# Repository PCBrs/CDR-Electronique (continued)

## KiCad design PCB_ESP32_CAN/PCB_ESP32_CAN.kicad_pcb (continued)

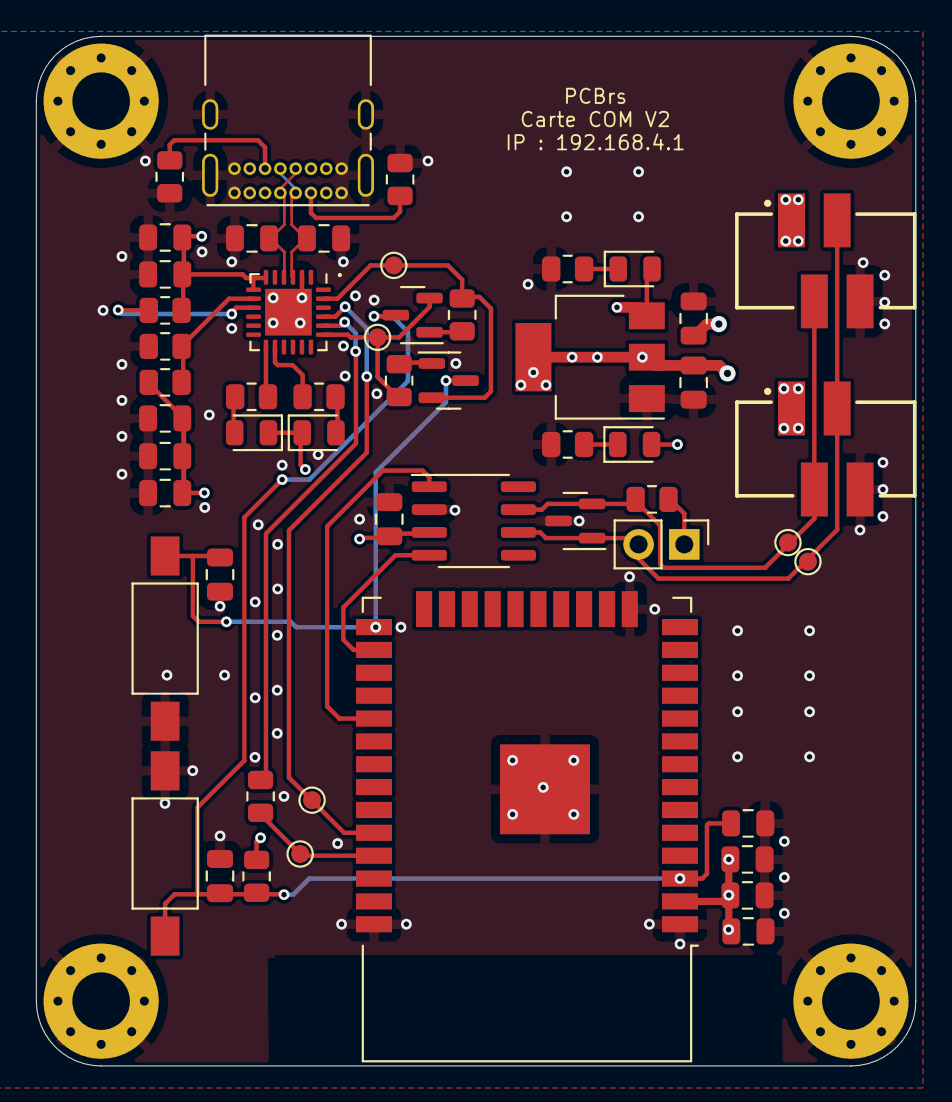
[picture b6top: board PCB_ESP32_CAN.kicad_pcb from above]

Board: 4 copper layers, 48.9 x 57.2 mm, 57 parts (0 on the bottom side), 29 nets.

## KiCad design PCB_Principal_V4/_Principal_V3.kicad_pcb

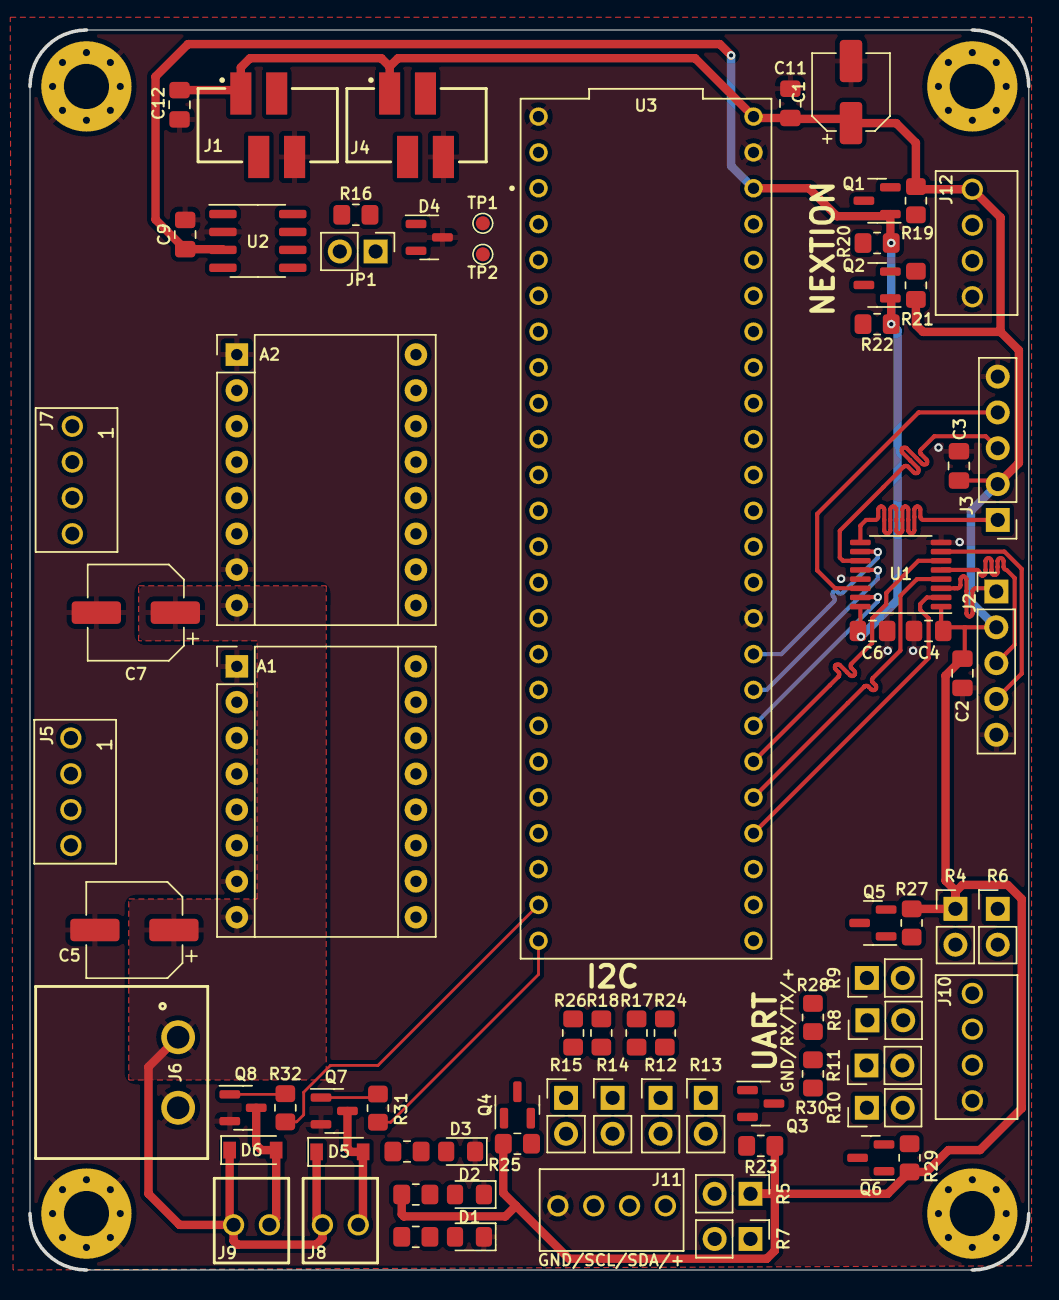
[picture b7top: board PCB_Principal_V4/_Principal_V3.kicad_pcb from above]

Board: 2 copper layers, 70.8 x 87.9 mm, 80 parts (0 on the bottom side), 67 nets.

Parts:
A1, A2: Pololu_Breakout_DRV8825; Pololu_Breakout-16_15.2x20.3mm
C1: 10u; CP_Elec_5x5.4
C2, C3, C4, C6, C9, C11: 100n; C_0805_2012Metric_Pad1.18x1.45mm_HandSolder
C5, C7: 47u; CP_Elec_6.3x5.4
C12: 10u; C_0805_2012Metric_Pad1.18x1.45mm_HandSolder
D1, D2, D3: LED; LED_0805_2012Metric_Pad1.15x1.40mm_HandSolder
D4: TVS; SOT-23
D5, D6: 1N4148W; D_SOD-123
H1, H2, H3, H4: MountingHole_Pad; MountingHole_3.2mm_M3_Pad_Via
J1, J4: CAN; 690367290476
J2: ENCODEUR_G; PinHeader_1x05_P2.54mm_Vertical
J3: ENCODEUR_D; PinHeader_1x05_P2.54mm_Vertical
J5: MOTOR_D; Wuerth_2.54mm_4pins_61900411121
J6: BATT; Wuerth_batcon_691313710002
J7: MOTOR_G; Wuerth_2.54mm_4pins_61900411121
J8, J9: FAN; Wuerth_2.54mm_2pins_61900211121
J10: UART; Wuerth_2.54mm_4pins_61900411121
J11: I2C; Wuerth_2.54mm_4pins_61900411121
J12: NEXTION; Wuerth_2.54mm_4pins_61900411121
JP1: 120; PinHeader_1x02_P2.54mm_Vertical
Q1, Q2, Q3, Q4, Q5, Q6: SI2302S; SOT-23
Q7, Q8: Q_NPN_BEC; SOT-23
R1, R17, R18: 4.7k; R_0805_2012Metric_Pad1.20x1.40mm_HandSolder
R2: 560; R_0805_2012Metric_Pad1.20x1.40mm_HandSolder
R3: 220; R_0805_2012Metric_Pad1.20x1.40mm_HandSolder
R4, R5, R6, R7, R8, R9, R10, R11, R12, R13, R14, R15: 0; PinHeader_1x02_P2.54mm_Vertical
R16: 120; R_0805_2012Metric_Pad1.20x1.40mm_HandSolder
R19, R20, R21, R22, R23, R24, R25, R26, R27, R28, R29, R30, R31, R32: 10k; R_0805_2012Metric_Pad1.20x1.40mm_HandSolder
TP1: CANH; TestPoint_Pad_D1.0mm
TP2: CANL; TestPoint_Pad_D1.0mm
U1: 4504; TSSOP-16_4.4x5mm_P0.65mm
U2: SN65HVD232; SOIC-8_3.9x4.9mm_P1.27mm
U3: TEENSY 4.1; Teensy_4-1

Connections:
+3V3: C6.2, C9.2, Q1.1 (G), Q2.1 (G), Q3.1 (G), Q4.1 (G), Q5.1 (G), Q6.1 (G), R3.1, R6.1, R7.1, R17.1, R18.1, R20.2, R22.2, R24.2, R26.2, R28.2, R30.2, U1.16 (VDD), U2.3 (VCC), U3.3.3V_1 (3.3V), U3.3.3V_2 (3.3V)
+5V: C1.1, C2.1, C3.1, C4.2, C11.1, C12.1, J1.1, J2.2, J3.2, J4.1, J12.1, R2.1, R4.1, R5.1, R19.2, R21.2, R23.2, R25.2, R27.2, R29.2, U1.1 (VCC), U3.VIN
+24V: A1.8 (VMOT), A2.8 (VMOT), C5.1, C7.1, D5.1 (K), D6.1 (K), J6.1, J8.1, J9.1, R1.1
/CANH: D4.1 (A1), J1.2, J4.2, R16.1, TP1.1, U2.7 (CANH)
/CANL: D4.2 (A2), J1.3, J4.3, JP1.2, TP2.1, U2.6 (CANL)
/CHANNEL_A_D: U1.12 (Eout), U3.40 (A16)
/CHANNEL_A_G: U1.4 (Bout), U3.37 (CS3)
/CHANNEL_B_D: U1.10 (Dout), U3.41 (A17)
/CHANNEL_B_G: U1.2 (Aout), U3.36 (CS2)
/CHANNEL_IDX_D: U1.15 (Fout), U3.39 (A15)
/CHANNEL_IDX_G: U1.6 (Cout), U3.38 (A14)
/DIR_D: A1.16 (DIR), U3.10 (CS1)
/DIR_G: A2.16 (DIR), U3.2 (OUT2)
/EN_D: A1.9 (~EN), U3.12 (MISO)
/EN_G: A2.9 (~EN), U3.4 (BCLK2)
/Level_shifter/IN: J12.2, J12.3, Q1.2 (D), Q2.2 (D), Q3.2 (D), Q4.2 (D), Q5.2 (D), Q6.2 (D), R9.1, R11.1, R13.1, R15.1, R19.1, R21.1, R23.1, R25.1, R27.1, R29.1
/M0_D: A1.10 (M0), U3.28 (RX7)
/M0_G: A2.10 (M0), U3.9 (OUT1C)
/M1_D: A1.11 (M1), U3.27 (A13)
/M1_G: A2.11 (M1), U3.8 (TX2)
/M2_D: A1.12 (M2), U3.26 (A12)
/M2_G: A2.12 (M2), U3.7 (RX2)
/NEXTION_RX: Q1.3 (S), R20.1, U3.0 (RX1)
/NEXTION_TX: Q2.3 (S), R22.1, U3.1 (TX1)
/PWM_FAN1: R31.1, U3.32 (OUT1B)
/PWM_FAN2: R32.1, U3.31 (CTX3)
/RST_D: A1.13 (~RST), U3.25 (A11)
/RST_G: A2.13 (~RST), U3.6 (OUT1D)
/RX: Q6.3 (S), R10.1, R30.1, U3.14 (A0)
/RX_CAN: U2.4 (R), U3.23 (A9)
/S1_D: J3.1, U1.9 (Din)
/S1_G: J2.1, U1.3 (Ain)
/S2_D: J3.3, U1.11 (Ein)
/S2_G: J2.3, U1.5 (Bin)
/S3_D: J3.4, U1.14 (Fin)
/S3_G: J2.4, U1.7 (Cin)
/SCL: Q4.3 (S), R14.1, R18.2, R26.1, U3.19 (A5)
/SDA: Q3.3 (S), R12.1, R17.2, R24.1, U3.18 (A4)
/SLP_D: A1.14 (~SLP), U3.24 (A10)
/SLP_G: A2.14 (~SLP), U3.5 (IN2)
/STP_D: A1.15 (STEP), U3.11 (MOSI)
/STP_G: A2.15 (STEP), U3.3 (LRCLK2)
/TX: Q5.3 (S), R8.1, R28.1, U3.15 (A1)
/TX_CAN: U2.1 (D), U3.22 (A8)
GND: A1.1 (GND), A1.7 (GND), A2.1 (GND), A2.7 (GND), C1.2, C2.2, C3.2, C4.1, C5.2, C6.1, C7.2, C9.1, C11.2, C12.2, D1.1 (K), D2.1 (K), D3.1 (K), D4.3 (common), H1.1, H2.1, H3.1, H4.1, J1.4, J2.5, J3.5, J4.4, J6.2, J10.4, J11.4, J12.4, Q7.2 (E), Q8.2 (E), U1.8 (VSS), U1.13 (Select), U2.2 (GND), U3.GND1 (GND), U3.GND2 (GND), U3.GND3 (GND)
unnamed: A1.3 (A2), J5.1
unnamed: A1.4 (A1), J5.2
unnamed: A1.5 (B1), J5.3
unnamed: A1.6 (B2), J5.4
unnamed: A2.3 (A2), J7.1
unnamed: A2.4 (A1), J7.2
unnamed: A2.5 (B1), J7.3
unnamed: A2.6 (B2), J7.4
unnamed: D1.2 (A), R1.2
unnamed: D2.2 (A), R2.2
unnamed: D3.2 (A), R3.2
unnamed: D5.2 (A), J8.2, Q7.3 (C)
unnamed: D6.2 (A), J9.2, Q8.3 (C)
unnamed: J10.1, R4.2, R6.2
unnamed: J10.2, R8.2, R9.2
unnamed: J10.3, R10.2, R11.2
unnamed: J11.1, R5.2, R7.2
unnamed: J11.2, R12.2, R13.2
unnamed: J11.3, R14.2, R15.2
unnamed: JP1.1, R16.2
unnamed: Q7.1 (B), R31.2
unnamed: Q8.1 (B), R32.2

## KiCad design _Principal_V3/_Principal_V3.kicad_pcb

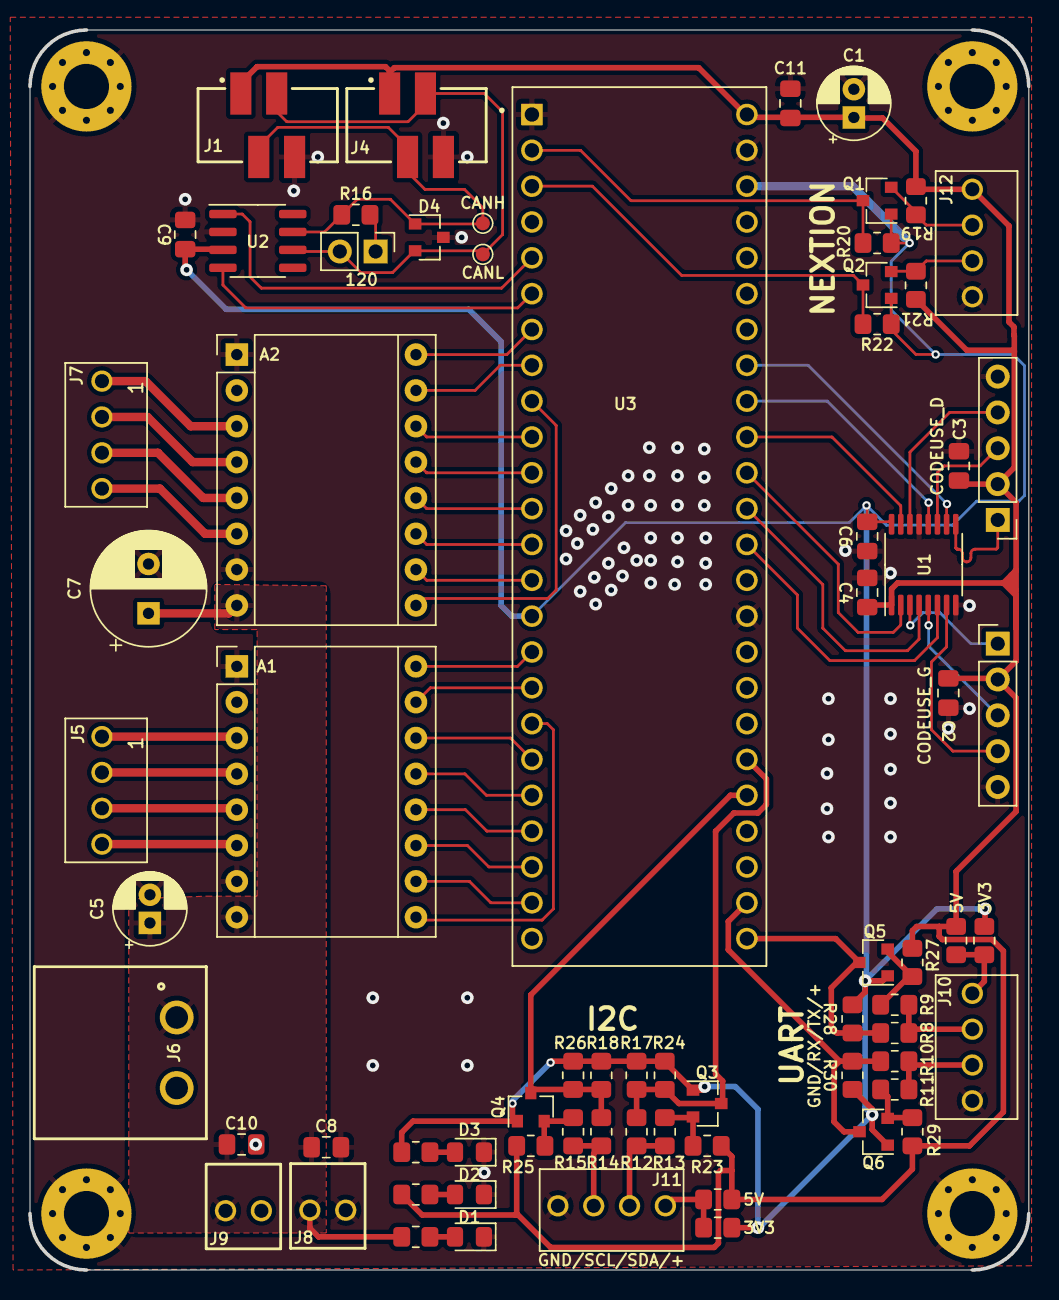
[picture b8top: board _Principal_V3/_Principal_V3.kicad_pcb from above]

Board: 2 copper layers, 70.8 x 87.9 mm, 75 parts (0 on the bottom side), 66 nets.

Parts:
3V3, 3V3#2, 5V, 5V#2: 0; R_0805_2012Metric_Pad1.20x1.40mm_HandSolder
120: 120; PinHeader_1x02_P2.54mm_Vertical
A1, A2: Pololu_Breakout_DRV8825; Pololu_Breakout-16_15.2x20.3mm
C1, C5: 10u; CP_Radial_D5.0mm_P2.00mm
C2, C3, C4, C6, C9, C11: 100n; C_0805_2012Metric_Pad1.18x1.45mm_HandSolder
C7: 10u; CP_Radial_D8.0mm_P3.50mm
C8, C10: 10u; C_0805_2012Metric_Pad1.18x1.45mm_HandSolder
CANH: CANH; TestPoint_Pad_D1.0mm
CANL: CANL; TestPoint_Pad_D1.0mm
CODEUSE_D: ENCODEUR_D; PinHeader_1x05_P2.54mm_Vertical
CODEUSE_G: ENCODEUR_G; PinHeader_1x05_P2.54mm_Vertical
D1, D2, D3: LED; LED_0805_2012Metric_Pad1.15x1.40mm_HandSolder
D4: TVS; SOT-23
H1, H2, H3, H4: MountingHole_Pad; MountingHole_3.2mm_M3_Pad_Via
J1, J4: CAN; 690367290476
J5: MOTOR_D; Wuerth_2.54mm_4pins_61900411121
J6: BATT; Wuerth_batcon_691313710002
J7: MOTOR_G; Wuerth_2.54mm_4pins_61900411121
J8, J9: FAN; Wuerth_2.54mm_2pins_61900211121
J10: UART; Wuerth_2.54mm_4pins_61900411121
J11: I2C; Wuerth_2.54mm_4pins_61900411121
J12: NEXTION; Wuerth_2.54mm_4pins_61900411121
Q1, Q2, Q3, Q4, Q5, Q6: SI2302S; SOT-23
R1, R17, R18: 4.7k; R_0805_2012Metric_Pad1.20x1.40mm_HandSolder
R2: 560; R_0805_2012Metric_Pad1.20x1.40mm_HandSolder
R3: 220; R_0805_2012Metric_Pad1.20x1.40mm_HandSolder
R8, R9, R10, R11, R12, R13, R14, R15: 0; R_0805_2012Metric_Pad1.20x1.40mm_HandSolder
R16: 120; R_0805_2012Metric_Pad1.20x1.40mm_HandSolder
R19, R20, R21, R22, R23, R24, R25, R26, R27, R28, R29, R30: 10k; R_0805_2012Metric_Pad1.20x1.40mm_HandSolder
U1: 4504; TSSOP-16_4.4x5mm_P0.65mm
U2: SN65HVD232; SOIC-8_3.9x4.9mm_P1.27mm
U3: DEV-14058; MODULE_DEV-14058

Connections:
+3V3: 3V3.1, 3V3#2.1, C6.2, C9.2, Q1.1 (G), Q2.1 (G), Q3.1 (G), Q4.1 (G), Q5.1 (G), Q6.1 (G), R3.1, R17.1, R18.1, R20.2, R22.2, R24.2, R26.2, R28.2, R30.2, U1.16 (VDD), U2.3 (VCC), U3.15 (3V3), U3.46 (3V3_250MA_MAX)
+5V: 5V.1, 5V#2.1, C1.1, C2.1, C3.1, C4.2, C11.1, CODEUSE_D.2, CODEUSE_G.2, J1.1, J4.1, J12.1, R2.1, R19.2, R21.2, R23.2, R25.2, R27.2, R29.2, U1.1 (VCC), U3.48 (VIN)
+24V: A1.8 (VMOT), A2.8 (VMOT), C5.1, C7.1, C8.1, C10.1, J6.1, J8.1, J9.1, R1.1
/CANH: CANH.1, D4.1 (A1), J1.2, J4.2, R16.1, U2.7 (CANH)
/CANL: 120.2, CANL.1, D4.2 (A2), J1.3, J4.3, U2.6 (CANL)
/CHANNEL_A_D: U1.12 (Eout), U3.40 (18/A4/SDA0/TOUCH)
/CHANNEL_A_G: U1.4 (Bout), U3.37 (15/A1/CS0/TOUCH)
/CHANNEL_B_D: U1.10 (Dout), U3.41 (19/A5/SCL0/TOUCH)
/CHANNEL_B_G: U1.2 (Aout), U3.38 (16/A2/PWM/SCL0/TOUCH)
/CHANNEL_IDX_D: U1.15 (Fout), U3.39 (17/A3/PWM/SDA0/TOUCH)
/CHANNEL_IDX_G: U1.6 (Cout), U3.36 (14/A0/PWM/SCK0)
/DIR_D: A1.16 (DIR), U3.16 (24)
/DIR_G: A2.16 (DIR), U3.7 (PWM/TX1/MISO1/5)
/EN_D: A1.9 (~EN), U3.18 (SCL2/TX1/26)
/EN_G: A2.9 (~EN), U3.9 (PWM/RX3/MOSI0/SCL0/7)
/Level_shifter/IN: J12.2, Q1.2 (D), R19.1
/M0_D: A1.10 (M0), U3.23 (A12/RX4/CS1/31)
/M0_G: A2.10 (M0), U3.14 (MISO0/12)
/M1_D: A1.11 (M1), U3.22 (PWM/CAN0RX/TOUCH/30)
/M1_G: A2.11 (M1), U3.13 (MOSI0/11)
/M2_D: A1.12 (M2), U3.21 (PWM/CAN0TX/TOUCH/29)
/M2_G: A2.12 (M2), U3.12 (PWM/TX2/CS0/10)
/NEXTION_RX: Q1.3 (S), R20.1, U3.2 (MOSI1/RX1/TOUCH/0)
/NEXTION_TX: Q2.3 (S), R22.1, U3.3 (MISO1/TX1/TOUCH/1)
/RST_D: A1.13 (~RST), U3.20 (MOSI0/28)
/RST_G: A2.13 (~RST), U3.11 (PWM/RX2/CS0/9)
/RX: Q6.3 (S), R10.1, R30.1, U3.26 (34/A15/CAN1RX/SDA0/RX5)
/RX_CAN: U2.4 (R), U3.6 (PWM/CAN0RX/SDA2/4)
/S1_D: CODEUSE_D.1, U1.9 (Din)
/S1_G: CODEUSE_G.1, U1.3 (Ain)
/S2_D: CODEUSE_D.3, U1.11 (Ein)
/S2_G: CODEUSE_G.3, U1.5 (Bin)
/S3_D: CODEUSE_D.4, U1.14 (Fin)
/S3_G: CODEUSE_G.4, U1.7 (Cin)
/SCL: Q4.3 (S), R14.1, R18.2, R26.1, U3.29 (37/A18/PWM/SCL1)
/SDA: Q3.3 (S), R12.1, R17.2, R24.1, U3.30 (38/A19/PWM/SDA1)
/SLP_D: A1.14 (~SLP), U3.19 (SCK0/RX1/27)
/SLP_G: A2.14 (~SLP), U3.10 (PWM/TX3/MISO0/SDA0/8)
/STP_D: A1.15 (STEP), U3.17 (25)
/STP_G: A2.15 (STEP), U3.8 (PWM/6)
/TX: Q5.3 (S), R8.1, R28.1, U3.25 (33/A14/CAN1TX/SCL0/TX5)
/TX_CAN: U2.1 (D), U3.5 (PWM/CAN0TX/SCL2/3)
/sheet6215AC10/IN: J12.3, Q2.2 (D), R21.1
/sheet6216B4BD/IN: Q4.2 (D), R15.1, R25.1
/sheet6220E40B/IN: Q5.2 (D), R9.1, R27.1
/sheet6220E40C/IN: Q6.2 (D), R11.1, R29.1
/sheet6216318E/IN: Q3.2 (D), R13.1, R23.1
GND: A1.1 (GND), A1.7 (GND), A2.1 (GND), A2.7 (GND), C1.2, C2.2, C3.2, C4.1, C5.2, C6.1, C7.2, C8.2, C9.1, C10.2, C11.2, CODEUSE_D.5, CODEUSE_G.5, D1.1 (K), D2.1 (K), D3.1 (K), D4.3 (common), H1.1, H2.1, H3.1, H4.1, J1.4, J4.4, J6.2, J8.2, J9.2, J10.4, J11.4, J12.4, U1.8 (VSS), U1.13 (Select), U2.2 (GND), U3.1 (GND), U3.34 (GND), U3.47 (AGND)
unnamed: A1.3 (A2), J5.1
unnamed: A1.4 (A1), J5.2
unnamed: A1.5 (B1), J5.3
unnamed: A1.6 (B2), J5.4
unnamed: A2.3 (A2), J7.1
unnamed: A2.4 (A1), J7.2
unnamed: A2.5 (B1), J7.3
unnamed: A2.6 (B2), J7.4
unnamed: D1.2 (A), R1.2
unnamed: D2.2 (A), R2.2
unnamed: D3.2 (A), R3.2
unnamed: 3V3.2, 5V.2, J10.1
unnamed: J10.2, R8.2, R9.2
unnamed: J10.3, R10.2, R11.2
unnamed: 3V3#2.2, 5V#2.2, J11.1
unnamed: J11.2, R12.2, R13.2
unnamed: J11.3, R14.2, R15.2
unnamed: 120.1, R16.2

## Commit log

2021-11-11 Clone area repo
2021-11-21 regime sur la carte esp32
2021-11-21 pdf et step pour esp32
2021-12-15 IO prete, Pompe finir sérigraphie, Alim+AX12 à faire
2022-01-14 new alim pcb
2022-01-15 finalizing routing for test pcb buck
2022-01-28 last version of alim v5
2022-02-16 some changes
2022-02-16 work on dev board
2022-03-05 lots of stuf
2022-04-07 pcb lidar/ax12/batt ready to fab
2022-04-07 PCB RMEAS ok to fab
2022-05-28 Beaucoup de chose
2022-06-19 modif carte alim
2022-06-19 V2.0 ESP32 pcb
2022-07-31 Maj carte alim
2022-09-23 MAJ principal + stepper
2022-10-10 update last PCBs
